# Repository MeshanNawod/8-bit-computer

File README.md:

# 8-Bit Breadboard Computer

An 8-bit computer built from logic chips, 555 timers and transistors,
simulated in Tinkercad Circuits and documented step by step, with the
reasoning and calculations behind each part.

**Website:** <https://meshannawod.github.io/8-bit-computer/>

> **Credit:** This project follows the design of **Ben Eater's 8-bit breadboard
> computer**. The architecture, module breakdown and most of the circuit ideas
> are his. Go watch the original series. It is one of the best ways to learn
> how a computer works:
> - Website: <https://eater.net/8bit>
> - YouTube playlist: <https://www.youtube.com/playlist?list=PLowKtXNTBypGqImE405J2565dvjafglHU>
>
> What's mine here: the Tinkercad simulations, the write-ups, and the
> worked calculations.

---

## How the computer works

Every module connects to one shared **8-bit bus**. On each clock pulse, the
control logic lets one module *write* to the bus and one or more modules
*read* from it.

| Module | Job |
|--------|-----|
| Clock | The heartbeat: every step happens on a clock pulse |
| A and B registers | Hold the two numbers being worked on |
| ALU | Adds or subtracts A and B |
| RAM + memory address register | 16 bytes for the program and data |
| Program counter | Points at the next instruction |
| Instruction register | Holds the current instruction |
| Control logic | Decides who uses the bus on each step |
| Output | Shows a number on 7-segment displays |

## Build progress

| # | Module | Main chips | Status | Docs |
|---|--------|------------|--------|------|
| 1 | Clock | LM555 ×3, 74HC04, 74HC08, 74HC32 | ✅ Simulated (parts 1A to 4A) | [Clock docs](docs/clock/README.md) |
| 2 | Registers (A, B, IR) | 74LS173, 74LS245 | ⏳ Planned | — |
| 3 | ALU (add/subtract) | 74LS283, 74LS86 | ⏳ Planned | — |
| 4 | RAM + memory address register | 74LS189, 74LS157, 74LS173 | ⏳ Planned | — |
| 5 | Program counter | 74LS161 | ⏳ Planned | — |
| 6 | Output display | 28C16 EEPROM, 74LS273, 7-segment | ⏳ Planned | — |
| 7 | Control logic | 28C16 EEPROM ×2, 74LS161, 74LS138 | ⏳ Planned | — |

## Module 1: Clock

| Part | What it adds | Key values | Result | Tinkercad | Write-up |
|------|--------------|-----------|--------|-----------|----------|
| 1A | Astable 555 | R1 1 kΩ, R2 100 kΩ, C 1 µF | **7.18 Hz** | [Open](https://www.tinkercad.com/things/l30rW27OBnZ-astable-555-timer-8-bit-computer-clock-part-1-a) | [01-astable.md](docs/clock/01-astable.md) |
| 1B | Speed knob | R2 = 1 kΩ + 1 MΩ pot | **0.72 to 480 Hz** | [Open](https://www.tinkercad.com/things/5Rx0vSOaq2a-astable-555-timer-8-bit-computer-clock-part-1b-) | [01-astable.md](docs/clock/01-astable.md#part-1b-adjustable-speed) |
| 2A | Monostable 555 | R 1 MΩ, C 0.1 µF | **110 ms** per press | [Open](https://www.tinkercad.com/things/hLZbnoHB4L6-monostable-555-timer-8-bit-computer-clock-part-2a) | [02-monostable.md](docs/clock/02-monostable.md) |
| 3 | Plain select switch | SPDT between 1B and 2A | auto / manual | [Open](https://www.tinkercad.com/things/8pzGGpFieEt-bistable-555-timer-8-bit-computer-clock-part-3b) | [03-bistable.md](docs/clock/03-bistable.md#part-3-plain-select-switch) |
| 3C | Bistable 555 | 2 × 1 kΩ pull-ups, SPDT | debounced switch | [Open](https://www.tinkercad.com/things/8nKWwN5A36f-monostable-555-timer-8-bit-computer-clock-part-3c) | [03-bistable.md](docs/clock/03-bistable.md#part-3c-bistable-555) |
| 3B | All three 555s | 1B + 2A + 3C | three LEDs | [Open](https://www.tinkercad.com/things/2x38PAtikeI-bistable-555-timer-8-bit-computer-clock-part-3b) | [03-bistable.md](docs/clock/03-bistable.md#part-3b-all-three-timers) |
| 4A | Clock logic | 74HC04, 74HC08, 74HC32 | one CLK signal | [Open](https://www.tinkercad.com/things/6YHy5r96IyL-clock-logic-8-bit-computer-clock-part-4a) | [04-clock-logic.md](docs/clock/04-clock-logic.md) |

CLK = (AST · SEL + MONO · SEL̅) · HLT̅

All values are read from the Tinkercad board exports in
[`hardware/tinkercad/`](hardware/tinkercad).

## Tinkercad simulations

- Part 1A, astable 555: <https://www.tinkercad.com/things/l30rW27OBnZ-astable-555-timer-8-bit-computer-clock-part-1-a>
- Part 1B, astable with pot: <https://www.tinkercad.com/things/5Rx0vSOaq2a-astable-555-timer-8-bit-computer-clock-part-1b->
- Part 2A, monostable 555: <https://www.tinkercad.com/things/hLZbnoHB4L6-monostable-555-timer-8-bit-computer-clock-part-2a>
- Part 3B, all three 555s: <https://www.tinkercad.com/things/2x38PAtikeI-bistable-555-timer-8-bit-computer-clock-part-3b>
- Part 3C, bistable 555: <https://www.tinkercad.com/things/8nKWwN5A36f-monostable-555-timer-8-bit-computer-clock-part-3c>
- Part 3, plain select switch: <https://www.tinkercad.com/things/8pzGGpFieEt-bistable-555-timer-8-bit-computer-clock-part-3b>
- Part 4A, clock logic: <https://www.tinkercad.com/things/6YHy5r96IyL-clock-logic-8-bit-computer-clock-part-4a>

## Diagrams

Redrawn as clean SVGs from Ben Eater's whiteboard drawings:

| Diagram | Shows |
|---------|-------|
| [555-internals.svg](images/diagrams/555-internals.svg) | Inside the 555: divider, comparators, SR latch, discharge transistor, reset |
| [555-astable.svg](images/diagrams/555-astable.svg) | Astable wiring with 1 kΩ, 100 kΩ, 1 µF and an LED |
| [555-monostable.svg](images/diagrams/555-monostable.svg) | Monostable wiring with 1 MΩ, 0.1 µF and a push button |
| [clock-logic.svg](images/diagrams/clock-logic.svg) | Clock select and halt logic (AND, OR, NOT) |
| [clock-logic-nand.svg](images/diagrams/clock-logic-nand.svg) | The same logic with 7 NAND gates |

## Background reading in this repo

- [How the 555 timer works inside](docs/basics/555-timer.md)
- [Transistors as switches, and building logic gates from them](docs/basics/transistors-and-gates.md)
- [LED current-limiting resistors](docs/basics/led-resistors.md)
- [Parts list](docs/parts-list.md)

## What's in this repository

| Folder or file | Contents |
|----------------|----------|
| `docs/clock/` | Write-ups and calculations for each clock part |
| `docs/basics/` | 555 internals, transistors and gates, LED resistors |
| `docs/parts-list.md` | Parts list for the clock module |
| `hardware/tinkercad/` | Eagle `.brd` exports of each Tinkercad circuit |
| `images/` | Tinkercad breadboard screenshots |
| `images/diagrams/` | Circuit and logic diagrams (SVG) |
| `index.html`, `site.js` | The project website (GitHub Pages) |

## Credits

- **Ben Eater** ([eater.net](https://eater.net), [YouTube](https://www.youtube.com/@BenEater)):
  original 8-bit computer design and video series this project follows.
- Simulations built in [Autodesk Tinkercad Circuits](https://www.tinkercad.com/circuits).
- Datasheets: Texas Instruments NE555 and 74HC/74LS series.

## License

Documentation and simulations: [MIT](LICENSE). The original 8-bit computer
design belongs to Ben Eater; see his site for his terms.

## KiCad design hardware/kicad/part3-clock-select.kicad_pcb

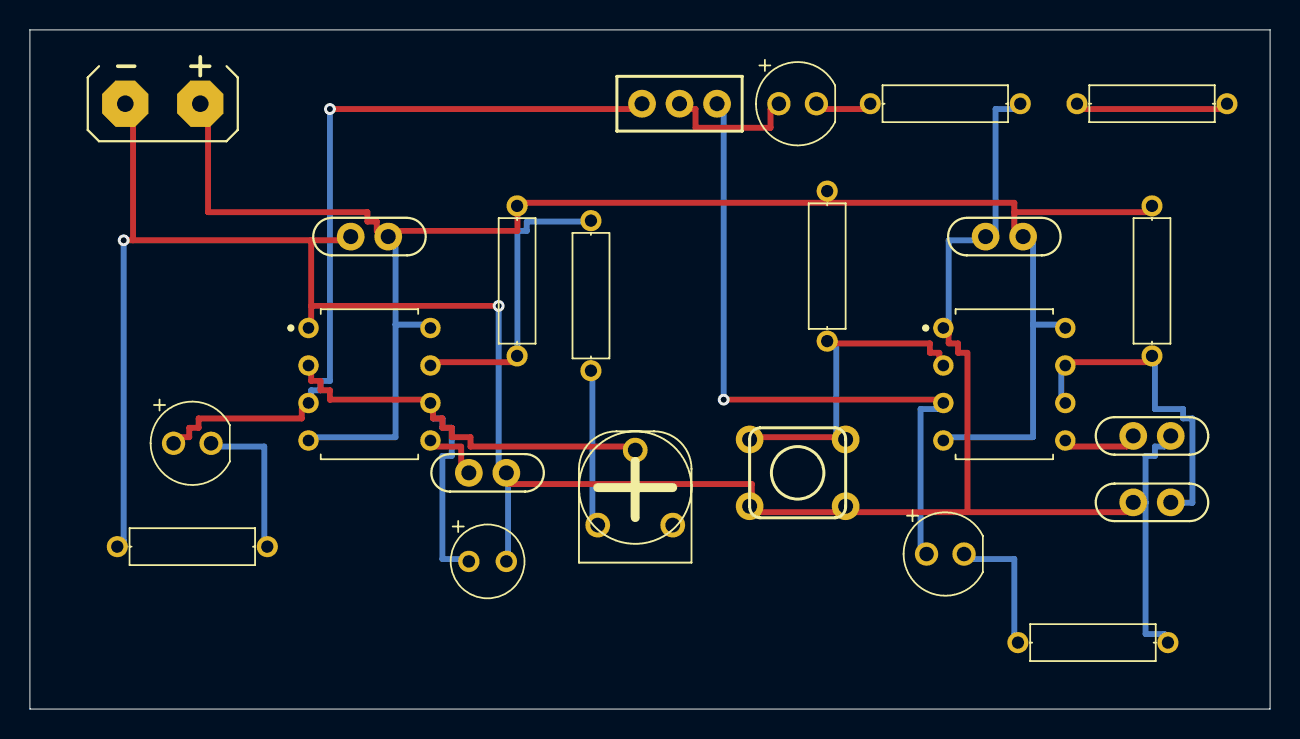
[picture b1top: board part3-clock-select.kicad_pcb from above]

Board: 2 copper layers, 84.0 x 46.0 mm, 23 parts (0 on the bottom side), 16 nets.

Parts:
C1, C2, C4, C5: 0.1u; CAP-THRU-2.54MM
C3: 1u; CAPPRD254W65D500H1150B
C6: 100n; CAP-THRU-2.54MM
D1: LED_RED; LEDRD254W60D565H860B
D2, D3: LED_YELLOW; LEDRD254W60D565H860B_Y
P1: BATTERYGENERIC; BATTERY-GENERIC
R1, R3, R4: 1k; RESAD1016W63L850D250B
R2, R5, R7, R8: 220; RESAD1016W63L850D250B
R6: 1M; RESAD1016W63L850D250B
RPOT2: 1M; HA-06-SM065
S1: SWITCH_MOMENTARY; SWITCH-MOMENTARY-PTH-6.5MM
S2: TOGGLE; SWITCH-SPDT-PTH-8.5X3.7MM
U1, U2: LM555_DIP; DIP826W53P254L959H508Q8B

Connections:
D1_C: D1.2, R2.2
D2_C: D2.2, R5.2
D3_C: D3.2, R7.1
P1+: C2.2, C4.2, P1.+, R1.2, R4.1, R6.2, U1.4, U1.8, U2.4, U2.8
P1-: C1.2, C2.1, C3.2, C4.1, C5.1, C6.2, P1.-, R2.1, R5.1, R7.2, S1.1, S1.2, U1.1, U2.1
R8_2: R8.1, R8.2
RPOT2_P$1: R3.1, RPOT2.1
S2_P: D3.1, S2.2
U1_CV: C6.1, U1.5
U1_DIS: C5.2, R6.1, U1.6, U1.7
U1_OUT: D2.1, S2.3, U1.3
U1_TR: R4.2, S1.3, S1.4, U1.2
U2_CV: C1.1, U2.5
U2_DIS: R1.1, R3.2, U2.7
U2_OUT: D1.1, S2.1, U2.3
U2_TR: C3.1, RPOT2.2, U2.2, U2.6

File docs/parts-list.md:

# Parts list

## Module 1: Clock, as built in Tinkercad (Part 3)

Taken from [part3-clock-select.brd](../hardware/tinkercad/part3-clock-select.brd).

| Qty | Ref | Part | Value | Where |
|-----|-----|------|-------|-------|
| 2 | U1, U2 | 555 timer | LM555 (DIP-8) | U2 astable, U1 monostable |
| 1 | RPOT2 | Potentiometer | 1 MΩ | Clock speed |
| 1 | R6 | Resistor | 1 MΩ | Monostable timing |
| 3 | R1, R3, R4 | Resistor | 1 kΩ | Astable R1, series with pot, button pull-up |
| 4 | R2, R5, R7, R8 | Resistor | 220 Ω | LEDs (R8 is unused, see Part 3 notes) |
| 1 | C3 | Electrolytic capacitor | 1 µF | Astable timing |
| 1 | C5 | Ceramic capacitor | 0.1 µF | Monostable timing |
| 2 | C1, C6 | Ceramic capacitor | 0.1 µF | 555 pin 5 filters |
| 2 | C2, C4 | Ceramic capacitor | 0.1 µF | Power-rail decoupling |
| 1 | S1 | Push button | momentary | Single step |
| 1 | S2 | Slide/toggle switch | SPDT | Auto/manual select |
| 1 | D1 | LED | red | Astable output |
| 2 | D2, D3 | LED | yellow | Monostable output, selected clock |
| 1 | — | Power supply | 5 V DC | Bench supply in the simulation |

## Still to add for the full clock module

| Qty | Part | Value | For |
|-----|------|-------|-----|
| 1 | 555 timer | LM555 | Bistable debounce of the select switch |
| 2 | Resistor | 1 kΩ | Bistable pull-ups |
| 1 | Ceramic capacitor | 0.1 µF | Bistable pin 5 filter |
| 1 | Hex inverter | 74LS04 | Clock logic |
| 1 | Quad AND | 74LS08 | Clock logic |
| 1 | Quad OR | 74LS32 | Clock logic |
| 3 | Ceramic capacitor | 0.1 µF | Decoupling for the logic chips |

## Discrete-transistor experiments (optional)

| Qty | Part | Value |
|-----|------|-------|
| 4 | NPN transistor | 2N3904 or BC547 |
| 4 | Resistor | 4.7 kΩ (base) |
| 2 | Resistor | 1 kΩ (collector/emitter) |

Parts for the later modules will be added as each one is built.
Ben Eater sells complete kits at <https://eater.net/8bit/kits>.

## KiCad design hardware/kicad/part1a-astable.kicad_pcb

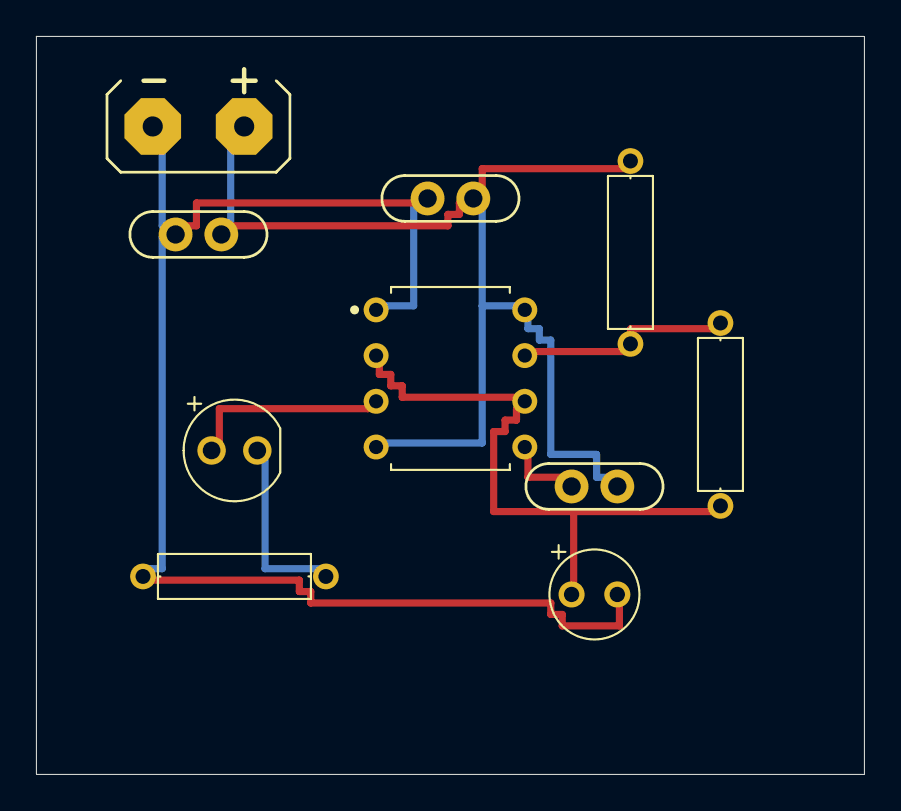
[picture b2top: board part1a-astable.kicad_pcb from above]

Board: 2 copper layers, 46.0 x 41.0 mm, 10 parts (0 on the bottom side), 7 nets.

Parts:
C1, C2, C4: 0.1u; CAP-THRU-2.54MM
C3: 1u; CAPPRD254W65D500H1150B
D1: LED_RED; LEDRD254W60D565H860B
P1: BATTERYGENERIC; BATTERY-GENERIC
R1: 1k; RESAD1016W63L850D250B
R2: 100k; RESAD1016W63L850D250B
R3: 220; RESAD1016W63L850D250B
U1: LM555_DIP; DIP826W53P254L959H508Q8B

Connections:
D1_C: D1.2, R3.2
P1+: C1.2, C2.2, C4.2, P1.+, R1.2, U1.4, U1.8
P1-: C2.1, C3.2, C4.1, P1.-, R3.1, U1.1
U1_CV: C1.1, U1.5
U1_DIS: R1.1, R2.1, U1.7
U1_OUT: D1.1, U1.3
U1_TR: C3.1, R2.2, U1.2, U1.6
